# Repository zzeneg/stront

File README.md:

# stront

Family of modular split keyboards with 38 or 40 keys, LCD display and Cirque/Azoteq trackpad.

## Features

All versions:
- Hotswap sockets
- LCD display (1.69" 240x280 by default)
- Cirque or Azoteq (with VIK adapter) trackpad
- roller/rotary encoders
- 3D printed cases
- exposed SPI/I2C contacts, so any other device can be used instead, it's just a matter of changing the case

|                                                    | MX-40              | MX-38              | Choc               |
| -------------------------------------------------- | ------------------ | ------------------ | ------------------ |
| Number of keys                                     | 40                 | 38                 | 38                 |
| Supported switches                                 | MX/KS<sup>[1]</sup>| MX/KS<sup>[1]</sup>| Choc v1            |
| Interconnect                                       | USB-C              | USB-C/TRRS         | USB-C/TRRS         |
| Interconnect                                       | USB-C              | USB-C/TRRS         | USB-C/TRRS         |
| [VIK](https://github.com/sadekbaroudi/vik) support | :heavy_check_mark: | :heavy_check_mark: | :x:                |
| Module system                                      | :heavy_check_mark: | :heavy_check_mark: | :x:                |
| Splay                                              | :x:                | :x:                | :heavy_check_mark: |

**[1]**: KS-33/KS-27 - Gateron Low Profile switches, not compatible with MX footprint and require special hotswap sockets

## Photos

#### MX-40 and MX-38 versions

#### MX-38 versions (MX and KS-33 switches)

#### Choc version

#### Display with PC companion app

https://github.com/zzeneg/stront/assets/910255/bb812821-9b2b-454a-a9a5-45d696a1f5aa

## Available modules - MX38/MX40 versions only ⚠️

- LCD displays
  - ST7789 1.69" 240x280
  - ST7789 2" 240x320
  - GC9A01 round 1.28" 240x240
- Touchpads
  - Cirque 40mm flat
  - Cirque 40mm curved
  - Azoteq TPS43
  - Azoteq TPS65 (technically supported but I think it's too big)

## Firmware

[Companion app](https://github.com/zzeneg/qmk-hid-host) for Raw HID communication.

#### QMK

Please see main `config.h` and `rules.mk` for comments and available options.

- [source code](https://github.com/zzeneg/qmk_firmware/tree/stront/keyboards/stront)
- [pre-compiled files](https://github.com/zzeneg/qmk_firmware/releases/tag/stront)

#### Vial

- [source code](https://github.com/zzeneg/vial-qmk/tree/feature/zzeneg/keyboards/stront)
- [pre-compiled files](https://github.com/zzeneg/vial-qmk/releases/tag/zzeneg)

#### Compiled versions
> Each firmware name has two modules, first is on the left side, second on the right, e.g. if your keyboard has Azoteq on the left and round display on the right - choose `azoteq-round`

- keymaps:
  - `default` - sample keymap with home row mods. Not recommended for longer use - create your own.
  - `hid` - default keymap with HID support. Requires companion application.
  - `zzeneg` - my highly customized layout.
- hardware versions:
  - `-rect-` - rectangular display (ST7789 240x280)
  - `-round-` - round display (GC9A01 240x240)
  - `-flat-` - flat 40mm Cirque
  - `-curved-` - curved 40mm Cirque
  - `-azoteq-` - Azoteq TPS43

> [!WARNING]
> For 38keys version with VIK display adapter - redefine LCD pins in `config.h` as in 40keys version

## Build Guide

[MX38/MX40 versions](./build-guide/mx/readme.md)

[Choc version](./build-guide/choc/readme.md)

## VIK - MX38/MX40 versions only ⚠️

> [!NOTE]
> VIK is a standard for a data interface between printed circuit boards. It is intended to provide modularity between a mechanical keyboard PCB and additional features.

[VIK repository](https://github.com/sadekbaroudi/vik)

#### Certification card

| Category               | Classification       | Response                          |
| ---------------------- | -------------------- | --------------------------------- |
| FPC connector          | Required             | :heavy_check_mark:                |
| Breakout pins          | Recommended          | :heavy_check_mark:                |
| Supplies: SPI          | Strongly recommended | :heavy_check_mark: <sup>[1]</sup> |
| Supplies: I2C          | Strongly recommended | :heavy_check_mark: <sup>[1]</sup> |
| I2C on main PCB        | Discouraged          | No                                |
| I2C pull ups           | Informative          | Optional<sup>[2]</sup>            |
| Supplies: RGB          | Strongly recommended | :heavy_check_mark:                |
| Supplies: Extra GPIO 1 | Required             | Digital                           |
| Supplies: Extra GPIO 2 | Required             | Digital                           |

**[1]**: I2C and SPI use same pins, so you can use only one or the other, not both. Selection is configured in firmware.

**[2]**: PCB has pads designed for 1206/3216 SMD resistors, you can solder them manually if needed.

#### VIK usage

Built-in display and trackpad use the same interface, so any additional VIK module will have to replace one of them (it's possible to combine other I2C modules with Azoteq). Depending on the size it can integrated into the cover or a standalone case.

All possible connectors support VIK - FPC horizontal on the back, FPC vertical on the front and the breakout pins.

## Support

If you like my work and want to support my future designs, please consider [sponsorship](https://github.com/sponsors/zzeneg), ordering from PCBWay using my shared projects - [Choc](https://www.pcbway.com/project/shareproject/Stront_low_profile_keyboard_85ec2664.html) or [MX38](https://www.pcbway.com/project/shareproject/Stront_MX_KS_33_keyboard_6a70e49a.html), or using [referral link](https://pcbway.com/g/3wpLAF) for signing up.

#### Sponsors

Thank you very much for your support!

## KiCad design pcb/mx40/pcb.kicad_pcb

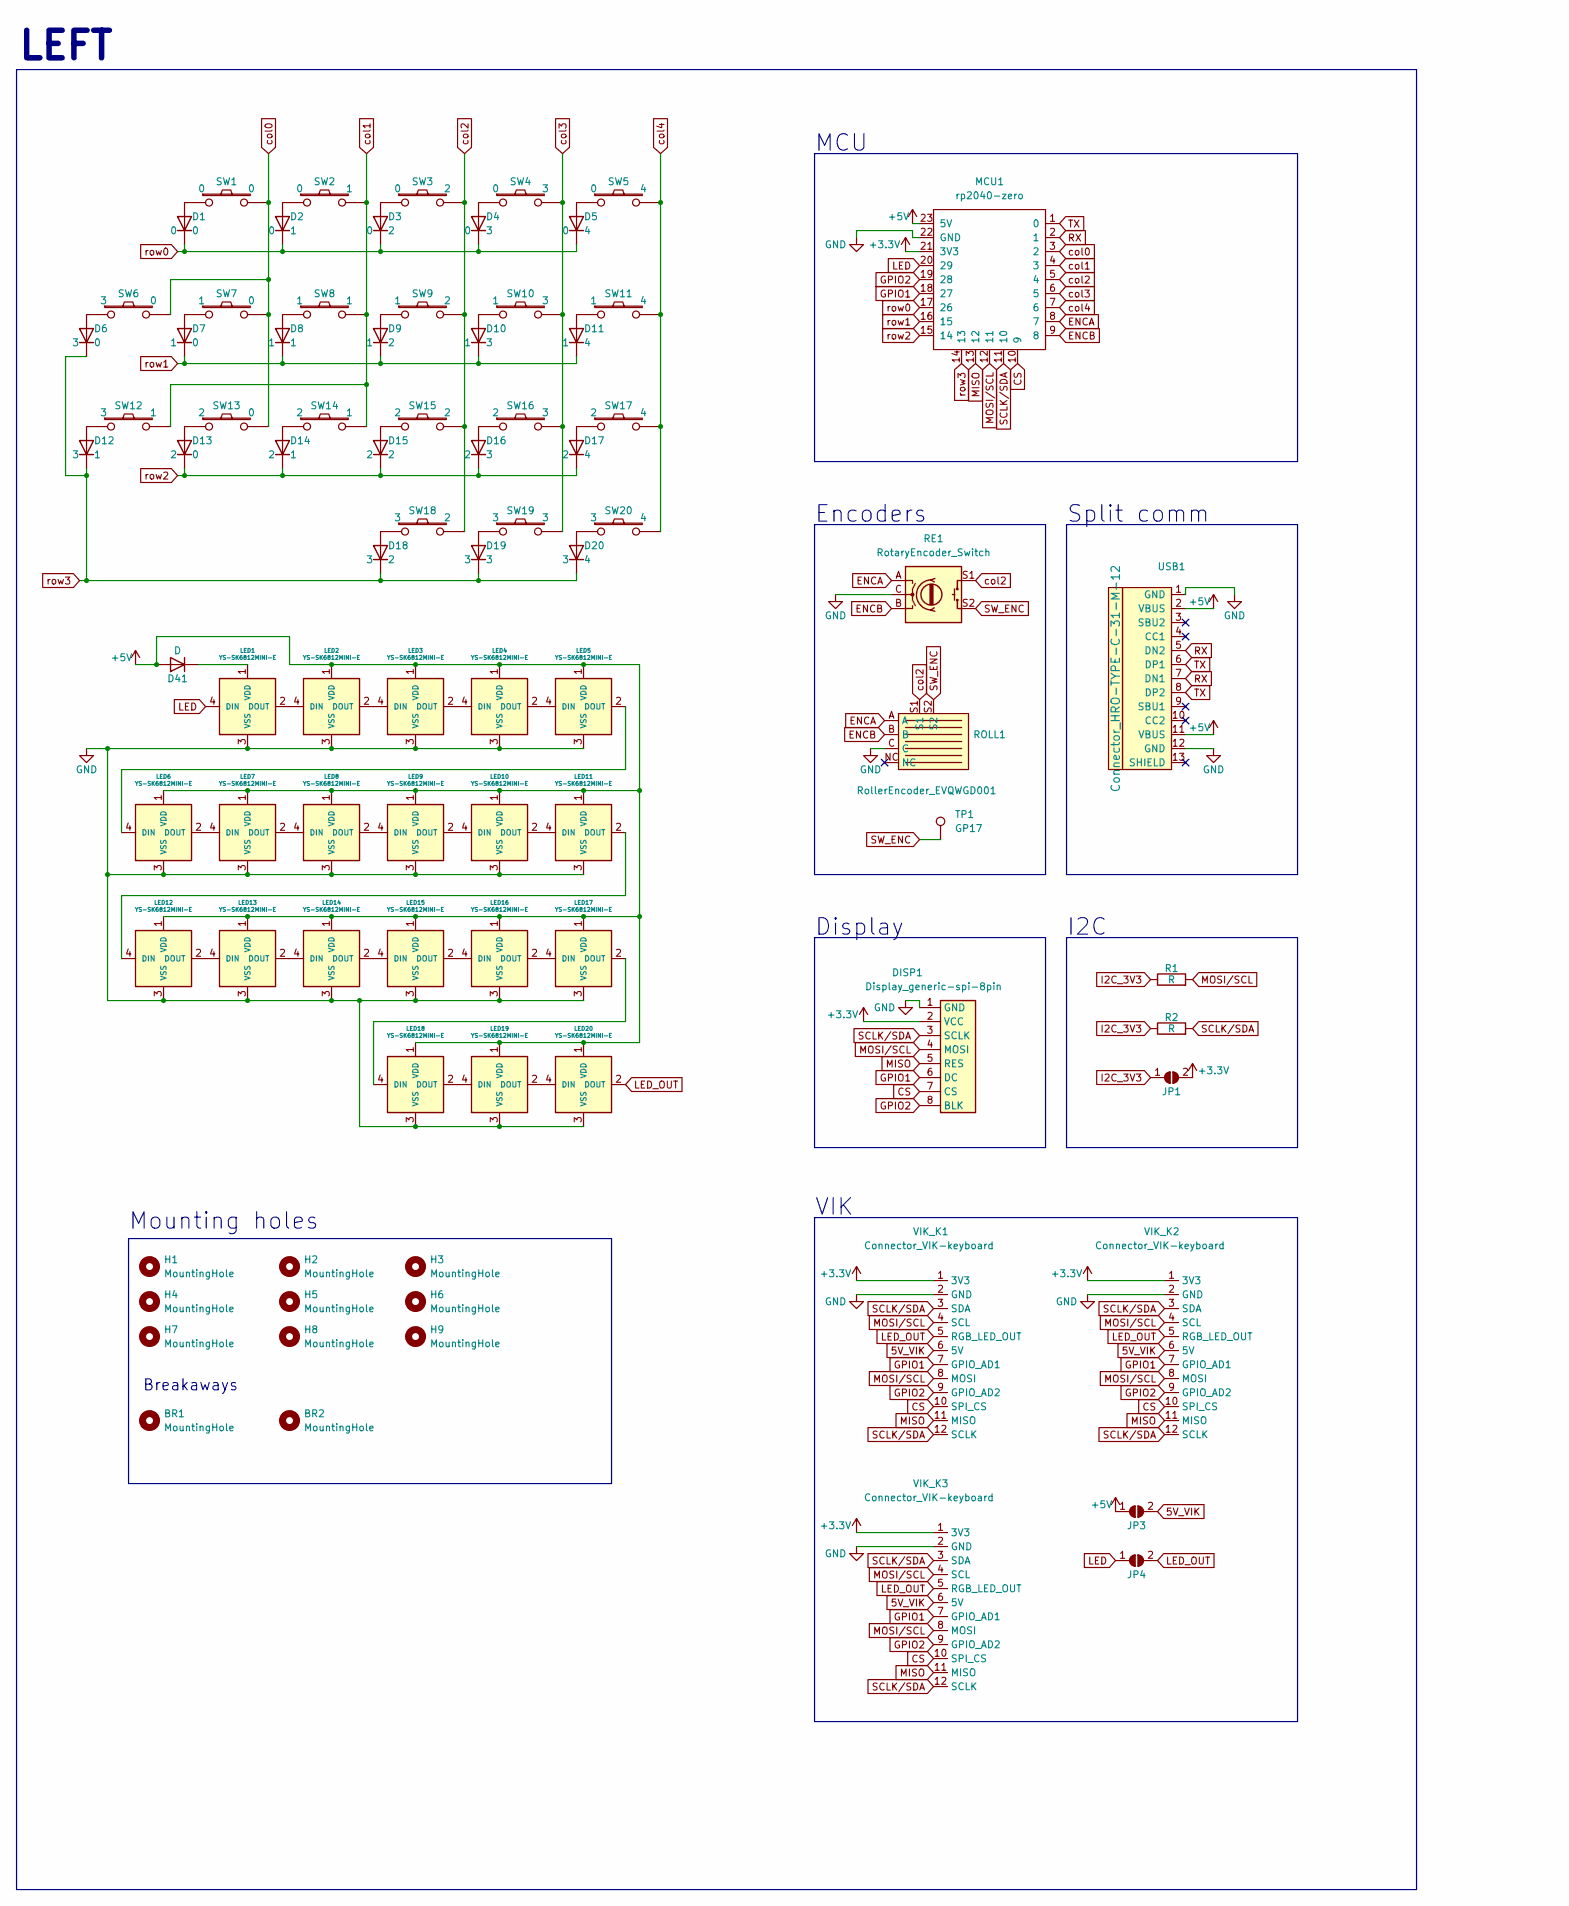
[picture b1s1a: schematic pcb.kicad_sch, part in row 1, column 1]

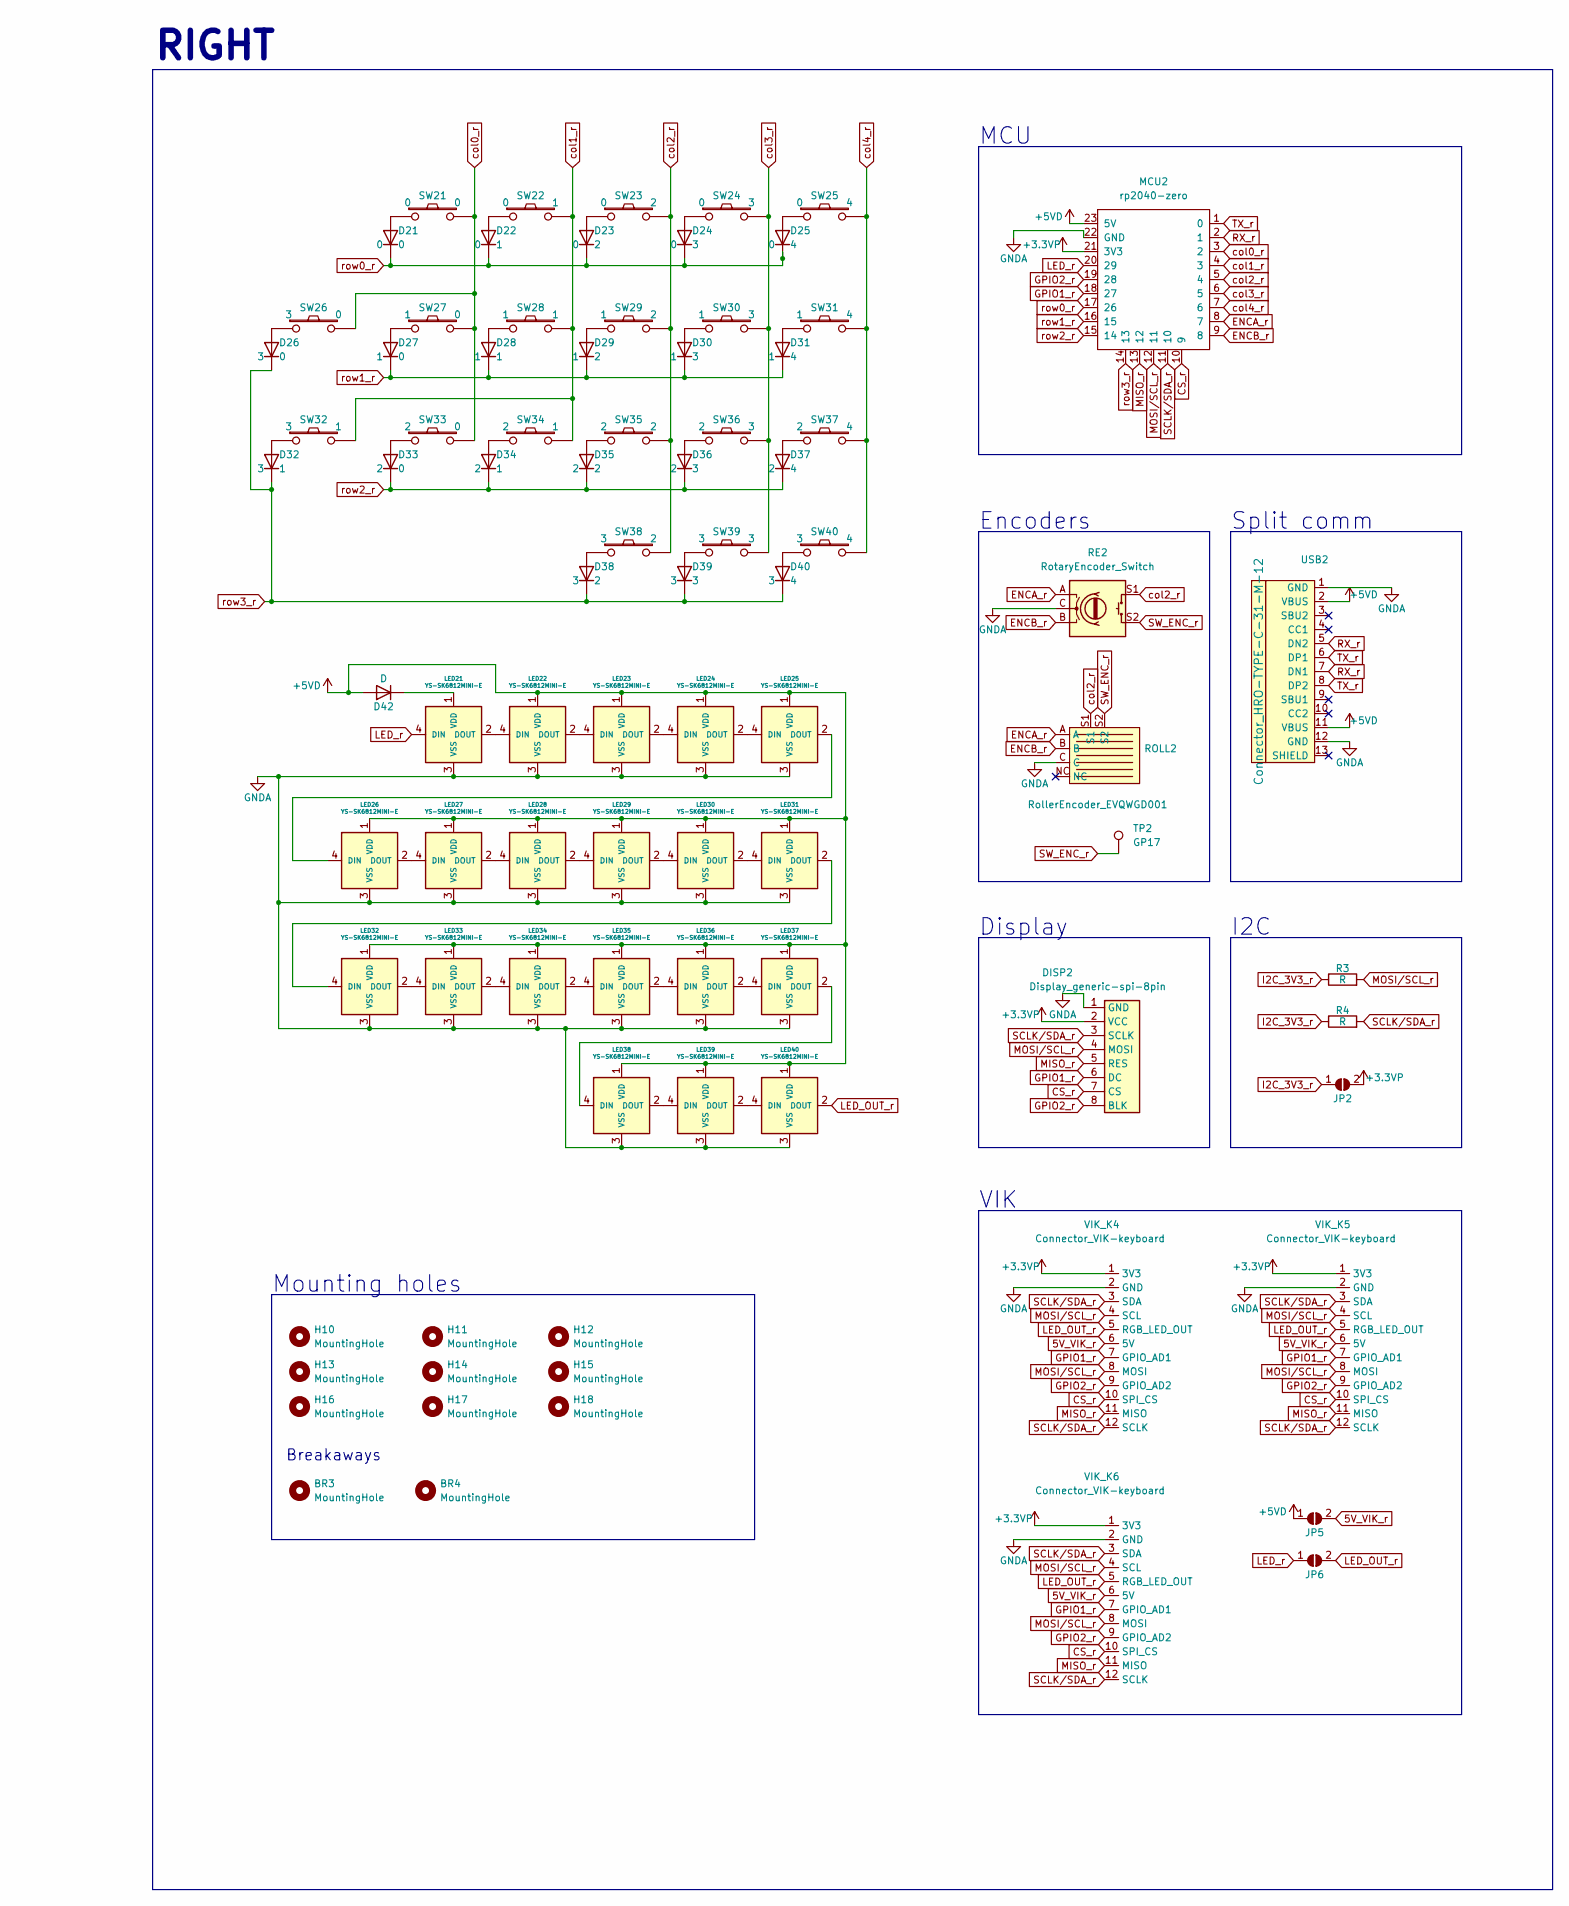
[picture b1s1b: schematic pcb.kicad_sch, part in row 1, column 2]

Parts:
BR1, BR2, BR3, BR4: MountingHole; Hole_Breakaway-Tabs
D1, D2, D3, D4, D5, D6, D7, D8, D9, D10, D11, D12, D13, D14, D15, D16, D17, D18, D19, D20, D21, D22, D23, D24, D25, D26, D27, D28, D29, D30, D31, D32, D33, D34, D35, D36, D37, D38, D39, D40, D41, D42: D; Diode_1N4148-SOD123
DISP1, DISP2: Display_generic-spi-8pin; Connector_Display-8pin-SPI-2.0mm
H1, H2, H3, H4, H5, H6, H7, H8, H9, H10, H11, H12, H13, H14, H15, H16, H17, H18: MountingHole; Hole_M2
JP1, JP2, JP3, JP4, JP5, JP6: SolderJumper_2_Open; SolderJumper-2_P1.3mm_Open_RoundedPad1.0x1.5mm
LED1, LED2, LED3, LED4, LED5, LED6, LED7, LED8, LED9, LED10, LED11, LED12, LED13, LED14, LED15, LED16, LED17, LED18, LED19, LED20, LED21, LED22, LED23, LED24, LED25, LED26, LED27, LED28, LED29, LED30, LED31, LED32, LED33, LED34, LED35, LED36, LED37, LED38, LED39, LED40: YS-SK6812MINI-E; LED_SK6812-MINI-E
MCU1, MCU2: rp2040-zero; MCU_rp2040-zero-tht
R1, R2, R3, R4: R; R_1206_3216Metric
RE1, RE2: RotaryEncoder_Switch; RotaryEncoder_EC11
ROLL1, ROLL2: RollerEncoder_EVQWGD001; RotaryEncoder_EVQWGD001
SW1, SW2, SW3, SW4, SW5, SW6, SW7, SW8, SW9, SW10, SW11, SW12, SW13, SW14, SW15, SW16, SW17, SW18, SW19, SW20, SW21, SW22, SW23, SW24, SW25, SW26, SW27, SW28, SW29, SW30, SW31, SW32, SW33, SW34, SW35, SW36, SW37, SW38, SW39, SW40: Switch; Switch_MXKS-hotswap-south
TP1, TP2: GP17; TestPoint_Pad_D1.5mm
USB1, USB2: Connector_HRO-TYPE-C-31-M-12; Connector_HRO-TYPE-C-31-M-12-data
VIK_K1, VIK_K4: Connector_VIK-keyboard; Connector_VIK-vertical-keyboard
VIK_K2, VIK_K5: Connector_VIK-keyboard; vik-keyboard-throughole
VIK_K3, VIK_K6: Connector_VIK-keyboard; vik-keyboard-connector-horizontal

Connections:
5V_VIK: JP3.2 (B), VIK_K1.6 (5V), VIK_K2.6 (5V), VIK_K3.6 (5V)
5V_VIK_r: JP5.2 (B), VIK_K4.6 (5V), VIK_K5.6 (5V), VIK_K6.6 (5V)
+3.3V: DISP1.2 (VCC), JP1.2 (B), MCU1.21 (3V3), VIK_K1.1 (3V3), VIK_K2.1 (3V3), VIK_K3.1 (3V3)
+3.3VP: DISP2.2 (VCC), JP2.2 (B), MCU2.21 (3V3), VIK_K4.1 (3V3), VIK_K5.1 (3V3), VIK_K6.1 (3V3)
+5V: D41.2 (A), JP3.1 (A), LED2.1 (VDD), LED3.1 (VDD), LED4.1 (VDD), LED5.1 (VDD), LED6.1 (VDD), LED7.1 (VDD), LED8.1 (VDD), LED9.1 (VDD), LED10.1 (VDD), LED11.1 (VDD), LED12.1 (VDD), LED13.1 (VDD), LED14.1 (VDD), LED15.1 (VDD), LED16.1 (VDD), LED17.1 (VDD), LED18.1 (VDD), LED19.1 (VDD), LED20.1 (VDD), MCU1.23 (5V), USB1.2 (VBUS), USB1.11 (VBUS)
+5VD: D42.2 (A), JP5.1 (A), LED22.1 (VDD), LED23.1 (VDD), LED24.1 (VDD), LED25.1 (VDD), LED26.1 (VDD), LED27.1 (VDD), LED28.1 (VDD), LED29.1 (VDD), LED30.1 (VDD), LED31.1 (VDD), LED32.1 (VDD), LED33.1 (VDD), LED34.1 (VDD), LED35.1 (VDD), LED36.1 (VDD), LED37.1 (VDD), LED38.1 (VDD), LED39.1 (VDD), LED40.1 (VDD), MCU2.23 (5V), USB2.2 (VBUS), USB2.11 (VBUS)
CS: DISP1.7 (CS), MCU1.10 (9), VIK_K1.10 (SPI_CS), VIK_K2.10 (SPI_CS), VIK_K3.10 (SPI_CS)
CS_r: DISP2.7 (CS), MCU2.10 (9), VIK_K4.10 (SPI_CS), VIK_K5.10 (SPI_CS), VIK_K6.10 (SPI_CS)
ENCA: MCU1.8 (7), RE1.A, ROLL1.A
ENCA_r: MCU2.8 (7), RE2.A, ROLL2.A
ENCB: MCU1.9 (8), RE1.B, ROLL1.B
ENCB_r: MCU2.9 (8), RE2.B, ROLL2.B
GND: DISP1.1 (GND), LED1.3 (VSS), LED2.3 (VSS), LED3.3 (VSS), LED4.3 (VSS), LED5.3 (VSS), LED6.3 (VSS), LED7.3 (VSS), LED8.3 (VSS), LED9.3 (VSS), LED10.3 (VSS), LED11.3 (VSS), LED12.3 (VSS), LED13.3 (VSS), LED14.3 (VSS), LED15.3 (VSS), LED16.3 (VSS), LED17.3 (VSS), LED18.3 (VSS), LED19.3 (VSS), LED20.3 (VSS), MCU1.22 (GND), RE1.C, ROLL1.C, USB1.1 (GND), USB1.12 (GND), VIK_K1.2 (GND), VIK_K2.2 (GND), VIK_K3.2 (GND)
GNDA: DISP2.1 (GND), LED21.3 (VSS), LED22.3 (VSS), LED23.3 (VSS), LED24.3 (VSS), LED25.3 (VSS), LED26.3 (VSS), LED27.3 (VSS), LED28.3 (VSS), LED29.3 (VSS), LED30.3 (VSS), LED31.3 (VSS), LED32.3 (VSS), LED33.3 (VSS), LED34.3 (VSS), LED35.3 (VSS), LED36.3 (VSS), LED37.3 (VSS), LED38.3 (VSS), LED39.3 (VSS), LED40.3 (VSS), MCU2.22 (GND), RE2.C, ROLL2.C, USB2.1 (GND), USB2.12 (GND), VIK_K4.2 (GND), VIK_K5.2 (GND), VIK_K6.2 (GND)
GPIO1: DISP1.6 (DC), MCU1.18 (27), VIK_K1.7 (GPIO_AD1), VIK_K2.7 (GPIO_AD1), VIK_K3.7 (GPIO_AD1)
GPIO1_r: DISP2.6 (DC), MCU2.18 (27), VIK_K4.7 (GPIO_AD1), VIK_K5.7 (GPIO_AD1), VIK_K6.7 (GPIO_AD1)
GPIO2: DISP1.8 (BLK), MCU1.19 (28), VIK_K1.9 (GPIO_AD2), VIK_K2.9 (GPIO_AD2), VIK_K3.9 (GPIO_AD2)
GPIO2_r: DISP2.8 (BLK), MCU2.19 (28), VIK_K4.9 (GPIO_AD2), VIK_K5.9 (GPIO_AD2), VIK_K6.9 (GPIO_AD2)
I2C_3V3: JP1.1 (A), R1.1, R2.1
I2C_3V3_r: JP2.1 (A), R3.1, R4.1
LED: JP4.1 (A), LED1.4 (DIN), MCU1.20 (29)
LED_OUT: JP4.2 (B), LED20.2 (DOUT), VIK_K1.5 (RGB_LED_OUT), VIK_K2.5 (RGB_LED_OUT), VIK_K3.5 (RGB_LED_OUT)
LED_OUT_r: JP6.2 (B), LED40.2 (DOUT), VIK_K4.5 (RGB_LED_OUT), VIK_K5.5 (RGB_LED_OUT), VIK_K6.5 (RGB_LED_OUT)
LED_r: JP6.1 (A), LED21.4 (DIN), MCU2.20 (29)
MISO: DISP1.5 (RES), MCU1.13 (12), VIK_K1.11 (MISO), VIK_K2.11 (MISO), VIK_K3.11 (MISO)
MISO_r: DISP2.5 (RES), MCU2.13 (12), VIK_K4.11 (MISO), VIK_K5.11 (MISO), VIK_K6.11 (MISO)
MOSI/SCL: DISP1.4 (MOSI), MCU1.12 (11), R1.2, VIK_K1.4 (SCL), VIK_K1.8 (MOSI), VIK_K2.4 (SCL), VIK_K2.8 (MOSI), VIK_K3.4 (SCL), VIK_K3.8 (MOSI)
MOSI/SCL_r: DISP2.4 (MOSI), MCU2.12 (11), R3.2, VIK_K4.4 (SCL), VIK_K4.8 (MOSI), VIK_K5.4 (SCL), VIK_K5.8 (MOSI), VIK_K6.4 (SCL), VIK_K6.8 (MOSI)
unnamed: D1.2 (A), SW1.1
unnamed: D2.2 (A), SW2.1
unnamed: D3.2 (A), SW3.1
unnamed: D4.2 (A), SW4.1
unnamed: D5.2 (A), SW5.1
unnamed: D6.2 (A), SW6.1
unnamed: D7.2 (A), SW7.1
unnamed: D8.2 (A), SW8.1
unnamed: D9.2 (A), SW9.1
unnamed: D10.2 (A), SW10.1
unnamed: D11.2 (A), SW11.1
unnamed: D12.2 (A), SW12.1
unnamed: D13.2 (A), SW13.1
unnamed: D14.2 (A), SW14.1
unnamed: D15.2 (A), SW15.1
unnamed: D16.2 (A), SW16.1
unnamed: D17.2 (A), SW17.1
unnamed: D18.2 (A), SW18.1
unnamed: D19.2 (A), SW19.1
unnamed: D20.2 (A), SW20.1
unnamed: D21.2 (A), SW21.1
unnamed: D22.2 (A), SW22.1
unnamed: D23.2 (A), SW23.1
unnamed: D24.2 (A), SW24.1
unnamed: D25.2 (A), SW25.1
unnamed: D26.2 (A), SW26.1
unnamed: D27.2 (A), SW27.1
unnamed: D28.2 (A), SW28.1
unnamed: D29.2 (A), SW29.1
unnamed: D30.2 (A), SW30.1
unnamed: D31.2 (A), SW31.1
unnamed: D32.2 (A), SW32.1
unnamed: D33.2 (A), SW33.1
unnamed: D34.2 (A), SW34.1
unnamed: D35.2 (A), SW35.1
unnamed: D36.2 (A), SW36.1
unnamed: D37.2 (A), SW37.1
unnamed: D38.2 (A), SW38.1
unnamed: D39.2 (A), SW39.1
unnamed: D40.2 (A), SW40.1
unnamed: D41.1 (K), LED1.1 (VDD)
unnamed: D42.1 (K), LED21.1 (VDD)
unnamed: LED1.2 (DOUT), LED2.4 (DIN)
unnamed: LED2.2 (DOUT), LED3.4 (DIN)
unnamed: LED3.2 (DOUT), LED4.4 (DIN)
unnamed: LED4.2 (DOUT), LED5.4 (DIN)
unnamed: LED5.2 (DOUT), LED6.4 (DIN)
unnamed: LED6.2 (DOUT), LED7.4 (DIN)
unnamed: LED7.2 (DOUT), LED8.4 (DIN)
unnamed: LED8.2 (DOUT), LED9.4 (DIN)
unnamed: LED9.2 (DOUT), LED10.4 (DIN)
unnamed: LED10.2 (DOUT), LED11.4 (DIN)
unnamed: LED11.2 (DOUT), LED12.4 (DIN)
unnamed: LED12.2 (DOUT), LED13.4 (DIN)
unnamed: LED13.2 (DOUT), LED14.4 (DIN)
unnamed: LED14.2 (DOUT), LED15.4 (DIN)
unnamed: LED15.2 (DOUT), LED16.4 (DIN)
unnamed: LED16.2 (DOUT), LED17.4 (DIN)
unnamed: LED17.2 (DOUT), LED18.4 (DIN)
unnamed: LED18.2 (DOUT), LED19.4 (DIN)
unnamed: LED19.2 (DOUT), LED20.4 (DIN)
unnamed: LED21.2 (DOUT), LED22.4 (DIN)
unnamed: LED22.2 (DOUT), LED23.4 (DIN)
unnamed: LED23.2 (DOUT), LED24.4 (DIN)
unnamed: LED24.2 (DOUT), LED25.4 (DIN)
unnamed: LED25.2 (DOUT), LED26.4 (DIN)
unnamed: LED26.2 (DOUT), LED27.4 (DIN)
unnamed: LED27.2 (DOUT), LED28.4 (DIN)
unnamed: LED28.2 (DOUT), LED29.4 (DIN)
unnamed: LED29.2 (DOUT), LED30.4 (DIN)
unnamed: LED30.2 (DOUT), LED31.4 (DIN)
unnamed: LED31.2 (DOUT), LED32.4 (DIN)
unnamed: LED32.2 (DOUT), LED33.4 (DIN)
unnamed: LED33.2 (DOUT), LED34.4 (DIN)
unnamed: LED34.2 (DOUT), LED35.4 (DIN)
unnamed: LED35.2 (DOUT), LED36.4 (DIN)
unnamed: LED36.2 (DOUT), LED37.4 (DIN)
unnamed: LED37.2 (DOUT), LED38.4 (DIN)
unnamed: LED38.2 (DOUT), LED39.4 (DIN)
unnamed: LED39.2 (DOUT), LED40.4 (DIN)
RX: MCU1.2 (1), USB1.5 (DN2), USB1.7 (DN1)
RX_r: MCU2.2 (1), USB2.5 (DN2), USB2.7 (DN1)
SCLK/SDA: DISP1.3 (SCLK), MCU1.11 (10), R2.2, VIK_K1.3 (SDA), VIK_K1.12 (SCLK), VIK_K2.3 (SDA), VIK_K2.12 (SCLK), VIK_K3.3 (SDA), VIK_K3.12 (SCLK)
SCLK/SDA_r: DISP2.3 (SCLK), MCU2.11 (10), R4.2, VIK_K4.3 (SDA), VIK_K4.12 (SCLK), VIK_K5.3 (SDA), VIK_K5.12 (SCLK), VIK_K6.3 (SDA), VIK_K6.12 (SCLK)
SW_ENC: RE1.S2, ROLL1.S2, TP1.1
SW_ENC_r: RE2.S2, ROLL2.S2, TP2.1
TX: MCU1.1 (0), USB1.6 (DP1), USB1.8 (DP2)
TX_r: MCU2.1 (0), USB2.6 (DP1), USB2.8 (DP2)
col0: MCU1.3 (2), SW1.2, SW6.2, SW7.2, SW13.2
col0_r: MCU2.3 (2), SW21.2, SW26.2, SW27.2, SW33.2
col1: MCU1.4 (3), SW2.2, SW8.2, SW12.2, SW14.2
col1_r: MCU2.4 (3), SW22.2, SW28.2, SW32.2, SW34.2
col2: MCU1.5 (4), RE1.S1, ROLL1.S1, SW3.2, SW9.2, SW15.2, SW18.2
col2_r: MCU2.5 (4), RE2.S1, ROLL2.S1, SW23.2, SW29.2, SW35.2, SW38.2
col3: MCU1.6 (5), SW4.2, SW10.2, SW16.2, SW19.2
col3_r: MCU2.6 (5), SW24.2, SW30.2, SW36.2, SW39.2
col4: MCU1.7 (6), SW5.2, SW11.2, SW17.2, SW20.2
col4_r: MCU2.7 (6), SW25.2, SW31.2, SW37.2, SW40.2
row0: D1.1 (K), D2.1 (K), D3.1 (K), D4.1 (K), D5.1 (K), MCU1.17 (26)
row0_r: D21.1 (K), D22.1 (K), D23.1 (K), D24.1 (K), D25.1 (K), MCU2.17 (26)
row1: D7.1 (K), D8.1 (K), D9.1 (K), D10.1 (K), D11.1 (K), MCU1.16 (15)
row1_r: D27.1 (K), D28.1 (K), D29.1 (K), D30.1 (K), D31.1 (K), MCU2.16 (15)
row2: D13.1 (K), D14.1 (K), D15.1 (K), D16.1 (K), D17.1 (K), MCU1.15 (14)
row2_r: D33.1 (K), D34.1 (K), D35.1 (K), D36.1 (K), D37.1 (K), MCU2.15 (14)
row3: D6.1 (K), D12.1 (K), D18.1 (K), D19.1 (K), D20.1 (K), MCU1.14 (13)
row3_r: D26.1 (K), D32.1 (K), D38.1 (K), D39.1 (K), D40.1 (K), MCU2.14 (13)

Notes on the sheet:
I2C
Breakaways
VIK
MCU
Encoders
Split comm
Display
LEFT
RIGHT
Mounting holes

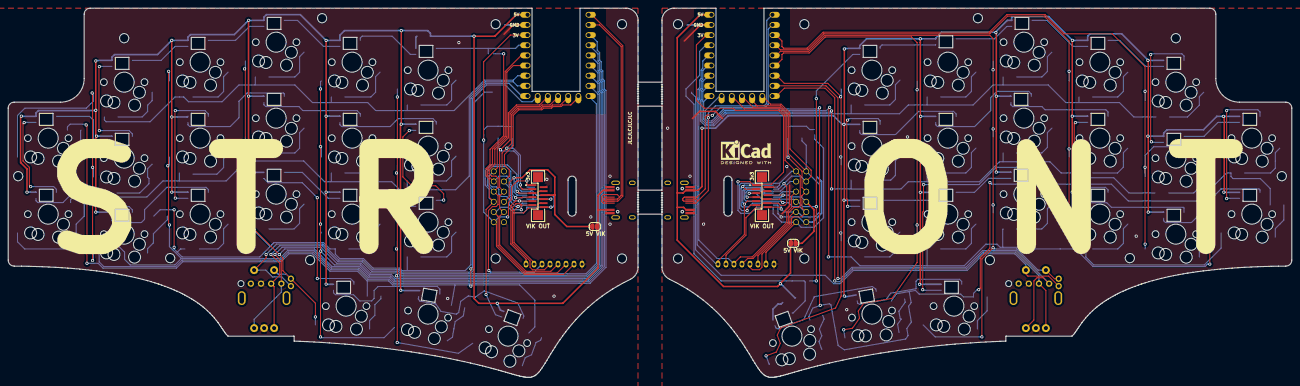
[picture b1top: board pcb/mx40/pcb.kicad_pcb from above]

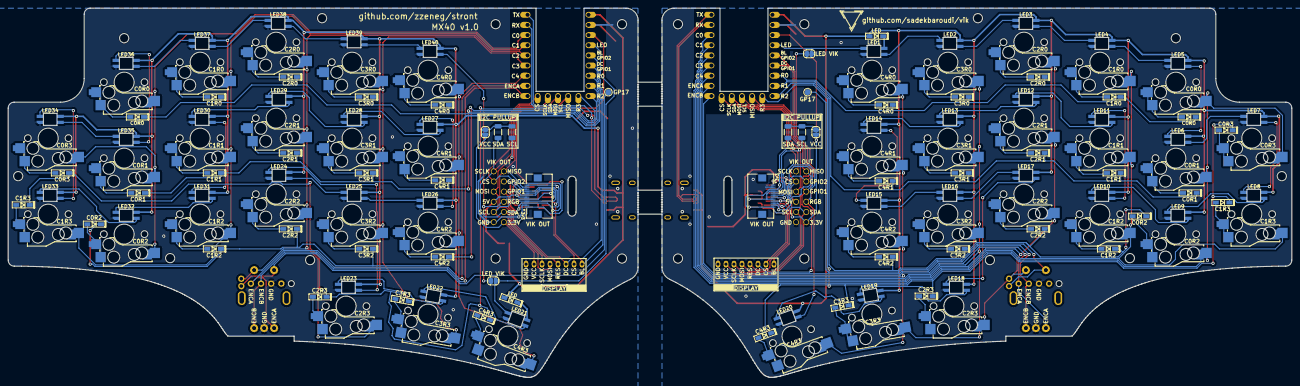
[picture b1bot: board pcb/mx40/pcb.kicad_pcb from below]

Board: 2 copper layers, 321.0 x 92.3 mm, 172 parts (94 on the bottom side), 134 nets.

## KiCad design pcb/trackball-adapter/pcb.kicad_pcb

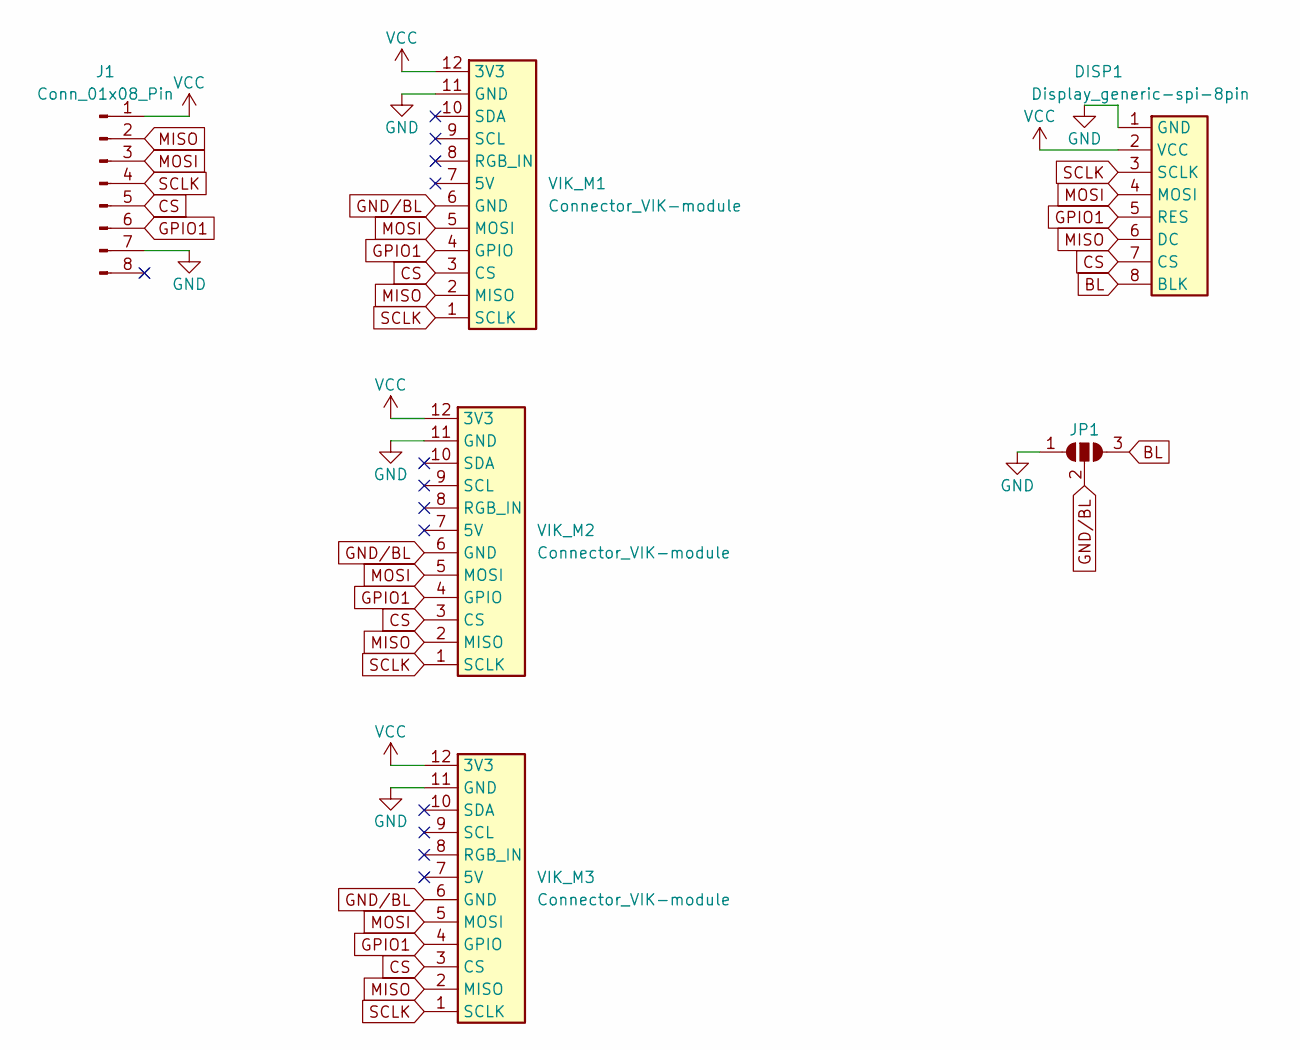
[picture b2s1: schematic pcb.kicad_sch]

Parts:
DISP1: Display_generic-spi-8pin; Connector_Display-8pin-SPI-2.0mm
J1: Conn_01x08_Pin; PinHeader_1x08_P2.54mm_Vertical
JP1: SolderJumper_3_Open; SolderJumper-3_P1.3mm_Open_RoundedPad1.0x1.5mm
VIK_M1: Connector_VIK-module; Connector_VIK-horizontal-keyboard
VIK_M2: Connector_VIK-module; Connector_VIK-vertical-keyboard
VIK_M3: Connector_VIK-module; Connector_VIK-adapter-keyboard

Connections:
BL: DISP1.8 (BLK), JP1.3 (B)
CS: DISP1.7 (CS), J1.5, VIK_M1.3 (CS), VIK_M2.3 (CS), VIK_M3.3 (CS)
GND: DISP1.1 (GND), J1.7, JP1.1 (A), VIK_M1.11 (GND), VIK_M2.11 (GND), VIK_M3.11 (GND)
GND/BL: JP1.2 (C), VIK_M1.6 (GND), VIK_M2.6 (GND), VIK_M3.6 (GND)
GPIO1: DISP1.5 (RES), J1.6, VIK_M1.4 (GPIO), VIK_M2.4 (GPIO), VIK_M3.4 (GPIO)
MISO: DISP1.6 (DC), J1.2, VIK_M1.2 (MISO), VIK_M2.2 (MISO), VIK_M3.2 (MISO)
MOSI: DISP1.4 (MOSI), J1.3, VIK_M1.5 (MOSI), VIK_M2.5 (MOSI), VIK_M3.5 (MOSI)
SCLK: DISP1.3 (SCLK), J1.4, VIK_M1.1 (SCLK), VIK_M2.1 (SCLK), VIK_M3.1 (SCLK)
VCC: DISP1.2 (VCC), J1.1, VIK_M1.12 (3V3), VIK_M2.12 (3V3), VIK_M3.12 (3V3)

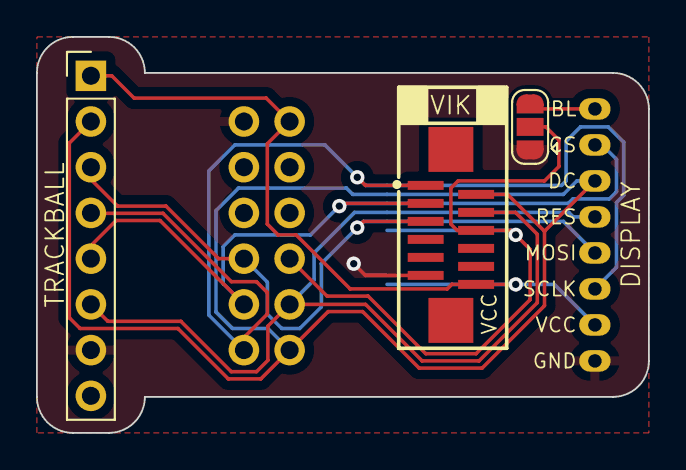
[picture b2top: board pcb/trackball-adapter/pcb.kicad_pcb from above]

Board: 2 copper layers, 34.0 x 22.0 mm, 6 parts (1 on the bottom side), 9 nets.

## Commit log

2023-02-03 reversible incomplete
2023-02-03 non-reversible schematic
2023-02-06 update libs
2023-02-06 draft 1
2023-02-07 prototype 0
2023-02-07 prototype 1
2023-02-11 small fix
2023-02-12 3d files for left
2023-02-12 add right
2023-02-12 project file
2023-02-28 component placement
2023-03-01 pcb left side
2023-03-02 pcb right side
2023-03-02 logos
2023-03-02 3d model
2023-03-02 gerber
2023-03-04 add pull up resistors, additional holes
2023-03-05 small rework and resize
2023-03-06 another resize
2023-03-07 update switch footprints
2023-03-07 final pcb
2023-03-08 case STLs
2023-03-09 final case
2023-03-14 plot references
2023-03-21 small case updates
2023-04-07 pictures and readme
2023-04-07 add video
2023-04-08 typo
2023-05-25 upload final firmware files
2023-05-30 add build guide
2023-05-30 fix video in readme
2023-06-09 Add MX version
2023-06-10 production files
2023-06-10 small updated
2023-06-10 3x5 version
2023-06-11 update components
2023-06-11 fix diode placement
2023-06-14 small updates
2023-06-17 hole updates
2023-06-23 new jumper for VIK
2023-06-24 fix PCBA placement
2023-06-24 add trackball adapter
2023-06-25 add case
2023-07-09 actually final case
2023-07-10 Update QMK repo link
2023-07-25 small case and cover updates
2023-07-26 photos and readme
2023-08-14 add VIAL firmware
2023-08-25 improve vial firmware
2023-08-25 small case updates (untested)
2023-09-07 add firmware for swapped trackpad/display sides
2023-10-11 Update readme.md
    fix #3
2024-01-20 remove untested case, add azoteq covers
2024-01-20 update firmware
2024-02-16 small improvements for azoteq covers - tested
2024-02-23 update readme, add azoteq
2024-03-11 remove libraries
2024-03-11 add first version
2024-03-11 fix case
2024-03-18 fix file names
2024-04-04 improve routing, rename case files
2024-04-07 replace vertical VIK footprint for easier soldering
2024-04-08 update 38keys to kicad 8, small routing updates, update libs
2024-04-08 add led position files
2024-04-08 update readmes, restructure
2024-04-19 update covers and mx40 bottom case
2024-04-20 update readmes
2024-04-24 update PCB silkscreen, fix readme
